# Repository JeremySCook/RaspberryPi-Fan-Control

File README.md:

# RaspberryPi Temperture Fan Control
Control a Raspberry Pi fan based on temperature. Four Possible methods:

* **Raspbery Pi OS Control** [as outlined here](https://www.youtube.com/watch?v=AdjU_AVcZTA)
* **temp-fan.sh script** provided in this directory. May want to install the full version of Raspberry Pi OS (even when running headless) to ensure the proper GPIO functionality is available. Some discussion on the subject: https://github.com/JeremySCook/RaspberryPi-Fan-Control/issues/2
* **Python Script** [found here](https://github.com/JeremySCook/RaspberryPi-Fan-Control/blob/master/PythonScript/fantemp.py)
* **True PWM Control** allows you to run the fan at different speeds. [Outlined on Instructables](https://www.instructables.com/PWM-Regulated-Fan-Based-on-CPU-Temperature-for-Ras/) by Aerandir14. 

Purchase the tiny EZ Fan2 control board at: http://jcdevices.com/

Note that the EZ Fan2 can be used for any small load up to a .6A limit (may need to de-rate in some situations) and fetures a flyback diode to help 
allieviate voltage spikes.

Further fan control/development info: https://www.youtube.com/watch?v=F1FQojoaNS8  
Control fan with Raspberry Pi OS: https://www.youtube.com/watch?v=AdjU_AVcZTA  
Control 12V fan (or other load) with the EZ Fan2: https://www.youtube.com/watch?v=bBBTj0RP7F8

Items used in video:

ICE Tower: https://amzn.to/2N95qrn [Amazon]  
2N2222 Transistor: https://amzn.to/2AK2vTy [Amazon]  
Heat Shrink: https://amzn.to/2C8qf3Z [Amazon]  

*note that Amazon links are affiliate, meaning I get a percentage of sales

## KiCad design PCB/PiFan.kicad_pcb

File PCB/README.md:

Through hole PCB info.

Previous version is found here. New version on Tindie uses surface mount components.

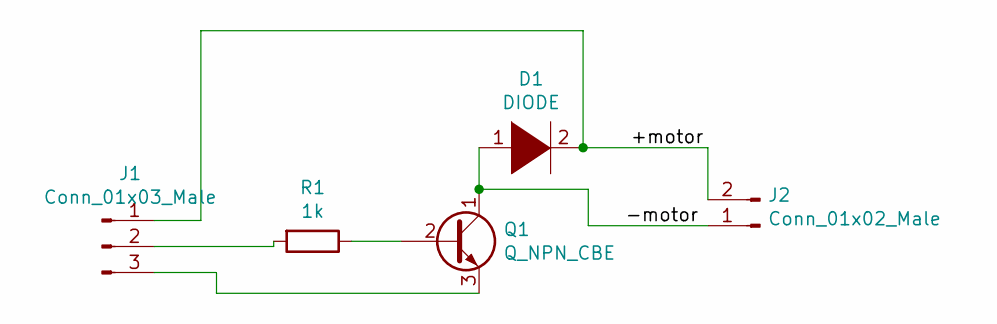
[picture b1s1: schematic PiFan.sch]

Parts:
D1: DIODE; D_DO-15_P3.81mm_Vertical_KathodeUp
J1: Conn_01x03_Male; PinHeader_1x03_P2.54mm_Horizontal
J2: Conn_01x02_Male; PinHeader_1x02_P2.54mm_Horizontal
Q1: Q_NPN_CBE; TO-92Flat
R1: 1k; R_Axial_DIN0204_L3.6mm_D1.6mm_P2.54mm_Vertical

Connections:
/+motor: D1.2 (A), J1.1, J2.2
/-motor: D1.1 (K), J2.1, Q1.1 (C)
unnamed: J1.2, R1.2
unnamed: J1.3, Q1.3 (E)
unnamed: Q1.2 (B), R1.1

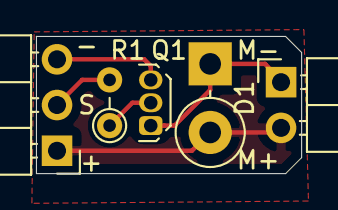
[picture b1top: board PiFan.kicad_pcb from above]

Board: 2 copper layers, 14.7 x 7.6 mm, 5 parts (0 on the bottom side), 5 nets.

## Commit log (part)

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2022-02-08 fixed broken print statement in python script
2023-05-04 Update fantemp.py to work on a temperature range
    Update fantemp.py to work on a temperature range
